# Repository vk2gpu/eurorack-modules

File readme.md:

Eurorack Modules
----------------

This is a collection of Eurorack modules that I've put together schematics, PCBs, and panels for.

Not all of these are my own original design, and appropriate credit and links to original source will be along side each with relevant license.

You will likely also need my Kicad footprint repo, which is located here: http://github.com/neilogd/kicad-footprints

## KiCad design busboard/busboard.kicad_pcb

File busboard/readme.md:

Busboard
--------

Basic busboard with +/-12v input with polyfuses, ~50Hz low pass filter in an attempt to reduce noise coming from/going back towards the PSU, and power indicator LEDs.
5V is not provided, but 5V, CV, and Gate pins are all connected.
Supports up to 8 modules, *should* be able to handle up to 1A on each rail.

Probably overkill, but a bit nicer than stripboard!

Feel free to use as you wish.

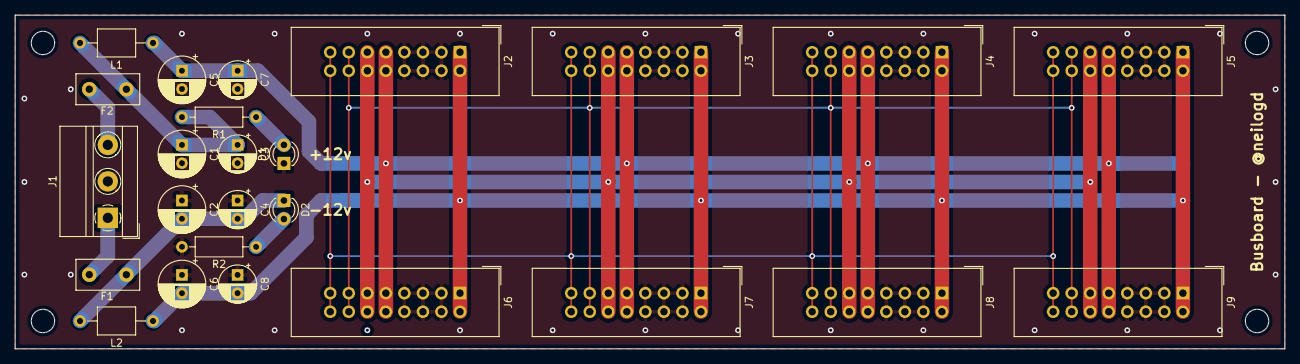
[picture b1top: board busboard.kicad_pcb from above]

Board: 2 copper layers, 174.0 x 45.7 mm, 25 parts (0 on the bottom side), 12 nets.

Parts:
C1, C2, C5, C6: 2000uF; CP_Radial_D6.3mm_P2.50mm
C3, C4, C7, C8: 270uF; CP_Radial_D5.0mm_P2.50mm
D1, D2: LED; LED_D3.0mm
F1, F2: Polyfuse; Fuse_Littelfuse_395Series
J1: Conn_01x03; TerminalBlock_MetzConnect_Type011_RT05503HBWC_1x03_P5.00mm_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
J2, J3, J4, J5, J6, J7, J8, J9: Conn_02x08_Odd_Even; IDC-Header_2x08_P2.54mm_Vertical
L1, L2: 10mH; L_Axial_L5.0mm_D3.6mm_P10.00mm_Horizontal_Murata_BL01RN1A2A2
R1, R2: 1k; R_Axial_DIN0207_L6.3mm_D2.5mm_P10.16mm_Horizontal

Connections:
+12V: C5.1, C7.1, J2.9, J2.10, J3.9, J3.10, J4.9, J4.10, J5.9, J5.10, J6.9, J6.10, J7.9, J7.10, J8.9, J8.10, J9.9, J9.10, L1.1
-12V: C6.2, C8.2, J2.1, J2.2, J3.1, J3.2, J4.1, J4.2, J5.1, J5.2, J6.1, J6.2, J7.1, J7.2, J8.1, J8.2, J9.1, J9.2, L2.1
GND: C1.2, C2.1, C3.2, C4.1, C5.2, C6.1, C7.2, C8.1, D1.1, J1.2, J2.3, J2.4, J2.5, J2.6, J2.7, J2.8, J3.3, J3.4, J3.5, J3.6, J3.7, J3.8, J4.3, J4.4, J4.5, J4.6, J4.7, J4.8, J5.3, J5.4, J5.5, J5.6, J5.7, J5.8, J6.3, J6.4, J6.5, J6.6, J6.7, J6.8, J7.3, J7.4, J7.5, J7.6, J7.7, J7.8, J8.3, J8.4, J8.5, J8.6, J8.7, J8.8, J9.3, J9.4, J9.5, J9.6, J9.7, J9.8, R2.2
unnamed: C1.1, C3.1, F2.1, L1.2, R1.2
unnamed: C2.2, C4.2, D2.1, F1.1, L2.2
unnamed: D1.2, R1.1
unnamed: D2.2, R2.1
unnamed: F1.2, J1.1
unnamed: F2.2, J1.3
unnamed: J2.11, J2.12, J3.11, J3.12, J4.11, J4.12, J5.11, J5.12, J6.11, J6.12, J7.11, J7.12, J8.11, J8.12, J9.11, J9.12
unnamed: J2.13, J2.14, J3.13, J3.14, J4.13, J4.14, J5.13, J5.14, J6.13, J6.14, J7.13, J7.14, J8.13, J8.14, J9.13, J9.14
unnamed: J2.15, J2.16, J3.15, J3.16, J4.15, J4.16, J5.15, J5.16, J6.15, J6.16, J7.15, J7.16, J8.15, J8.16, J9.15, J9.16

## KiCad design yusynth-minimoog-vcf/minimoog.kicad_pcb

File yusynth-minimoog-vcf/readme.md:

Yusynth Minimoog VCF
--------------------

Based on http://www.yusynth.net/Modular/EN/MOOGVCF/index.html

As per all Yusynth modules, this is for private use only.

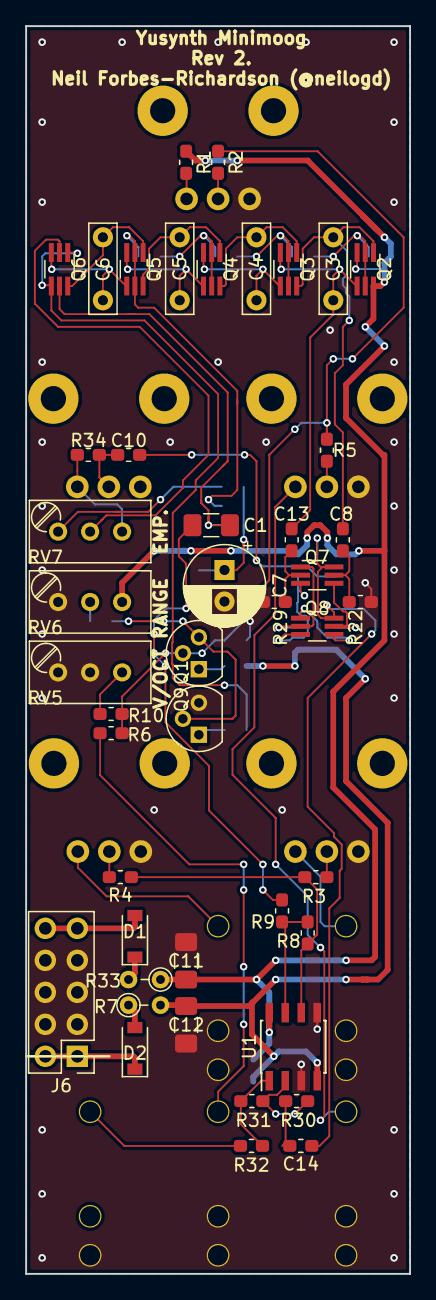
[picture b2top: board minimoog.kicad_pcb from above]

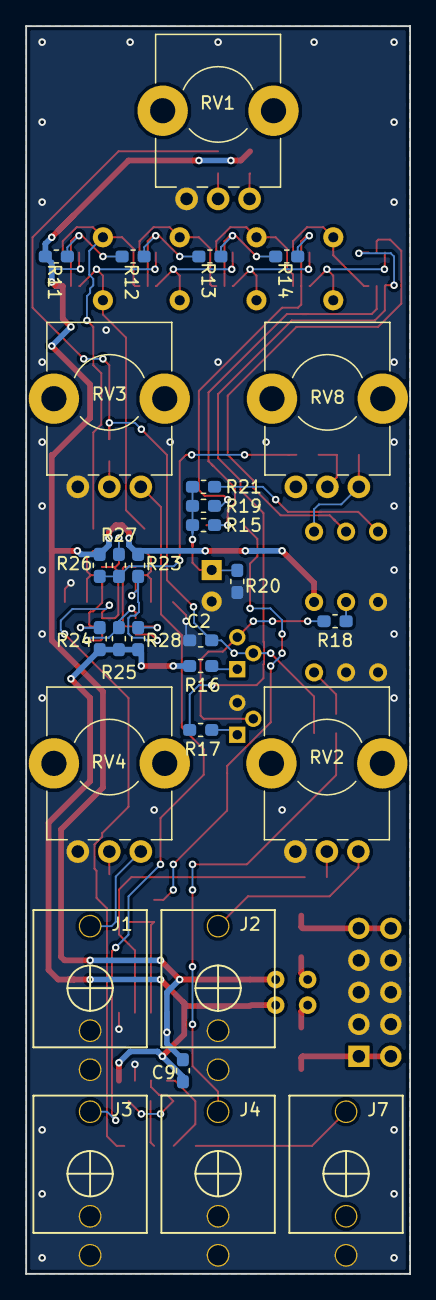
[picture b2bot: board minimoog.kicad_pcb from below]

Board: 2 copper layers, 30.5 x 99.1 mm, 74 parts (29 on the bottom side), 56 nets.

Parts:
C1: 10u; C_1206_3216Metric_Pad1.42x1.75mm_HandSolder
C2: 100p; C_0603_1608Metric_Pad1.05x0.95mm_HandSolder
C3, C4, C5, C6: 47n; C_Rect_L7.0mm_W2.0mm_P5.00mm
C7: 220u; CP_Radial_D6.3mm_P2.50mm
C8, C13: 220n; C_0603_1608Metric_Pad1.05x0.95mm_HandSolder
C9: 100n; C_0603_1608Metric_Pad1.05x0.95mm_HandSolder
C10, C14: 10u; C_0603_1608Metric_Pad1.05x0.95mm_HandSolder
C11, C12: 22u; C_1206_3216Metric_Pad1.42x1.75mm_HandSolder
D1, D2: 1N4004; D_SOD-123
J1, J2, J3, J4, J7: Jack; PJ301M-12
J6: EURO_PWR_2x5; Pin_Header_Straight_2x05_Pitch2.54mm
Q1: BC557; TO-92
Q2, Q3, Q4, Q5, Q6, Q7, Q8: NPN; SOT-363_SC-70-6_Handsoldering
Q9: BC547; TO-92
R1: 680; R_0603_1608Metric_Pad1.05x0.95mm_HandSolder
R2: 150k; R_0603_1608Metric_Pad1.05x0.95mm_HandSolder
R3, R4, R31: 120k; R_0603_1608Metric_Pad1.05x0.95mm_HandSolder
R5, R6, R18, R34: 100k; R_0603_1608Metric_Pad1.05x0.95mm_HandSolder
R7, R33: 10; R_Axial_DIN0204_L3.6mm_D1.6mm_P2.54mm_Vertical
R8, R30: 56k; R_0603_1608Metric_Pad1.05x0.95mm_HandSolder
R9: 10k; R_0603_1608Metric_Pad1.05x0.95mm_HandSolder
R10: 1.8k; R_0603_1608Metric_Pad1.05x0.95mm_HandSolder
R11, R21: 330; R_0603_1608Metric_Pad1.05x0.95mm_HandSolder
R12, R13, R14, R19: 150; R_0603_1608Metric_Pad1.05x0.95mm_HandSolder
R15, R16: 470; R_0603_1608Metric_Pad1.05x0.95mm_HandSolder
R17, R27, R32: 1k; R_0603_1608Metric_Pad1.05x0.95mm_HandSolder
R20: 220; R_0603_1608Metric_Pad1.05x0.95mm_HandSolder
R22, R29: 47k; R_0603_1608Metric_Pad1.05x0.95mm_HandSolder
R23: 22; R_0603_1608Metric_Pad1.05x0.95mm_HandSolder
R24, R28: 200k; R_0603_1608Metric_Pad1.05x0.95mm_HandSolder
R25: 910; R_0603_1608Metric_Pad1.05x0.95mm_HandSolder
R26: 180; R_0603_1608Metric_Pad1.05x0.95mm_HandSolder
RV1: B10K; Potentiometer_Alps_RK09K_Horizontal
RV2, RV4: A50K; Potentiometer_Alps_RK09K_Horizontal
RV3, RV8: B50K; Potentiometer_Alps_RK09K_Horizontal
RV5: 500; Potentiometer_Trimmer_Bourns_3296W
RV6: 10K; Potentiometer_Trimmer_Bourns_3296W
RV7: 1K; Potentiometer_Trimmer_Bourns_3296W
U1: TL072; SOIC-8_3.9x4.9mm_P1.27mm

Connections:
+12V: C9.1, C11.1, Q2.3, Q2.6, R1.1, R7.1, R11.1, R23.1, R26.1, RV6.3, U1.8
-12V: C9.2, C12.2, R16.2, R24.2, R25.2, R28.2, R33.2, U1.4
GND: C2.2, C7.2, C11.2, C12.1, J1.1, J1.2, J2.1, J2.2, J3.1, J3.2, J4.1, J4.2, J6.3, J6.4, J6.5, J6.6, J6.7, J6.8, J7.1, Q9.3, R20.2, R22.2, R29.2, RV1.3, RV2.3, RV3.3, RV4.3, RV5.1, RV5.2, RV6.1, U1.3, U1.5
unnamed: C1.1, Q6.5, R15.1
unnamed: C1.2, R9.1
unnamed: C2.1, Q1.2, R2.1, R5.1, R6.1, R10.1
unnamed: C3.1, C8.1, Q2.1, Q3.6
unnamed: C4.1, Q3.1, Q4.6
unnamed: C4.2, Q3.4, Q4.3
unnamed: C5.1, Q4.4, Q5.3
unnamed: C5.2, Q4.1, Q5.6
unnamed: C6.1, Q5.1, Q6.6
unnamed: C6.2, Q5.4, Q6.3
unnamed: C7.1, R15.2, R19.2, R20.1, R21.2
unnamed: C8.2, Q7.5, R22.1
unnamed: C10.1, R26.2, R27.1
unnamed: C10.2, R34.1, RV8.2
unnamed: C3.2, C13.1, Q2.4, Q3.3
unnamed: C13.2, Q7.2, R29.1
unnamed: C14.1, Q7.6, Q8.6, R27.2
unnamed: C14.2, R30.2
unnamed: D1.1, R7.2
unnamed: D1.2, J6.9, J6.10
unnamed: D2.1, J6.1, J6.2
unnamed: D2.2, R33.1
unnamed: J1.3, RV4.1
unnamed: J2.3, RV2.1
unnamed: J3.3, RV3.1
unnamed: J4.3, R6.2
unnamed: J7.3, R32.1
unnamed: Q1.1, R16.1
unnamed: Q1.3, Q9.2, R18.2
unnamed: Q2.2, Q2.5, R11.2, R12.1
unnamed: Q3.2, Q3.5, R12.2, R13.1
unnamed: Q4.2, Q4.5, R13.2, R14.1
unnamed: Q5.2, Q5.5, R14.2, R19.1
unnamed: Q6.1, Q6.4, R17.1
unnamed: Q6.2, RV7.2
unnamed: Q7.1, Q8.2, R28.1
unnamed: Q7.3, Q8.3, R23.2
unnamed: Q7.4, Q8.5, R24.1
unnamed: Q8.1, Q8.4, R25.1
unnamed: Q9.1, R17.2
unnamed: R1.2, RV1.1
unnamed: R2.2, RV1.2
unnamed: R3.1, R4.1, R8.2, U1.6
unnamed: R3.2, RV4.2
unnamed: R4.2, RV2.2
unnamed: R5.2, RV3.2
unnamed: R8.1, R9.2, U1.7
unnamed: R10.2, RV5.3
unnamed: R18.1, RV6.2
unnamed: R21.1, RV7.1
unnamed: R30.1, R31.2, U1.2
unnamed: R31.1, R32.2, U1.1
unnamed: R34.2, RV7.3, RV8.1

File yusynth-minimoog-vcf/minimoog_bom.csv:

Id;Designator;Package;Quantity;Designation;Supplier and ref
1;R34,R5,R6,R18;R_0603_1608Metric_Pad1.05x0.95mm_HandSolder;4;100k;
2;C7;CP_Radial_D6.3mm_P2.50mm;1;220u;
3;C14,C10;C_0603_1608Metric_Pad1.05x0.95mm_HandSolder;2;10u;
4;R7,R33;R_Axial_DIN0204_L3.6mm_D1.6mm_P2.54mm_Vertical;2;10;
5;Q1;TO-92;1;BC557;Any similar transistor should do
6;Q9;TO-92;1;BC547;Any similar transistor should do
7;D2,D1;D_SOD-123;2;1N4004;Any similar diode should do
8;J6;Pin_Header_Straight_2x05_Pitch2.54mm;1;EURO_PWR_2x5;
9;U1;SOIC-8_3.9x4.9mm_P1.27mm;1;TL072;
10;R28,R24;R_0603_1608Metric_Pad1.05x0.95mm_HandSolder;2;200k;
11;C6,C5,C4,C3;C_Rect_L7.0mm_W2.0mm_P5.00mm;4;47n;Film caps
12;Q5,Q8,Q7,Q4,Q3,Q2,Q6;SOT-363_SC-70-6_Handsoldering;7;NPN;NST45011MW6T1G
13;C2;C_0603_1608Metric_Pad1.05x0.95mm_HandSolder;1;100p;
14;C13,C8;C_0603_1608Metric_Pad1.05x0.95mm_HandSolder;2;220n;
15;C9;C_0603_1608Metric_Pad1.05x0.95mm_HandSolder;1;100n;
16;C11,C12;C_1206_3216Metric_Pad1.42x1.75mm_HandSolder;2;22u;
17;C1;C_1206_3216Metric_Pad1.42x1.75mm_HandSolder;1;10u;
18;R1;R_0603_1608Metric_Pad1.05x0.95mm_HandSolder;1;680;
19;R23;R_0603_1608Metric_Pad1.05x0.95mm_HandSolder;1;22;
20;R10;R_0603_1608Metric_Pad1.05x0.95mm_HandSolder;1;1.8k;
21;R11,R21;R_0603_1608Metric_Pad1.05x0.95mm_HandSolder;2;330;
22;R12,R13,R14,R19;R_0603_1608Metric_Pad1.05x0.95mm_HandSolder;4;150;
23;R8,R30;R_0603_1608Metric_Pad1.05x0.95mm_HandSolder;2;56k;
24;R2;R_0603_1608Metric_Pad1.05x0.95mm_HandSolder;1;150k;
25;R3,R4,R31;R_0603_1608Metric_Pad1.05x0.95mm_HandSolder;3;120k;
26;R15,R16;R_0603_1608Metric_Pad1.05x0.95mm_HandSolder;2;470;
27;R9;R_0603_1608Metric_Pad1.05x0.95mm_HandSolder;1;10k;
28;R26;R_0603_1608Metric_Pad1.05x0.95mm_HandSolder;1;180;
29;R25;R_0603_1608Metric_Pad1.05x0.95mm_HandSolder;1;910;
30;R29,R22;R_0603_1608Metric_Pad1.05x0.95mm_HandSolder;2;47k;
31;R32,R17,R27;R_0603_1608Metric_Pad1.05x0.95mm_HandSolder;3;1k;
32;R20;R_0603_1608Metric_Pad1.05x0.95mm_HandSolder;1;220;
33;J3,J7,J1,J4,J2;PJ301M-12;5;Jack;
34;RV4,RV2;Potentiometer_Alps_RK09K_Horizontal;2;A50K;
35;RV5;Potentiometer_Trimmer_Bourns_3296W;1;500;
36;RV6;Potentiometer_Trimmer_Bourns_3296W;1;10K;
37;RV7;Potentiometer_Trimmer_Bourns_3296W;1;1K;
38;RV3,RV8;Potentiometer_Alps_RK09K_Horizontal;2;B50K;
39;RV1;Potentiometer_Alps_RK09K_Horizontal;1;B10K;
;;;;;
;;http://www.yusynth.net/Modular/EN/MOOGVCF/index.html;;;

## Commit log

2019-05-09 Yusynth minimoog project
2019-05-09 Yusynth Minimoog VCF readme
2019-05-09 Readme.md
2019-05-09 kicad footprints
2019-05-10 Busboard added
2019-05-15 Fixed input 2 text on panel
2019-05-16 Added start of prototype helpers
2019-05-16 Added gitignore
